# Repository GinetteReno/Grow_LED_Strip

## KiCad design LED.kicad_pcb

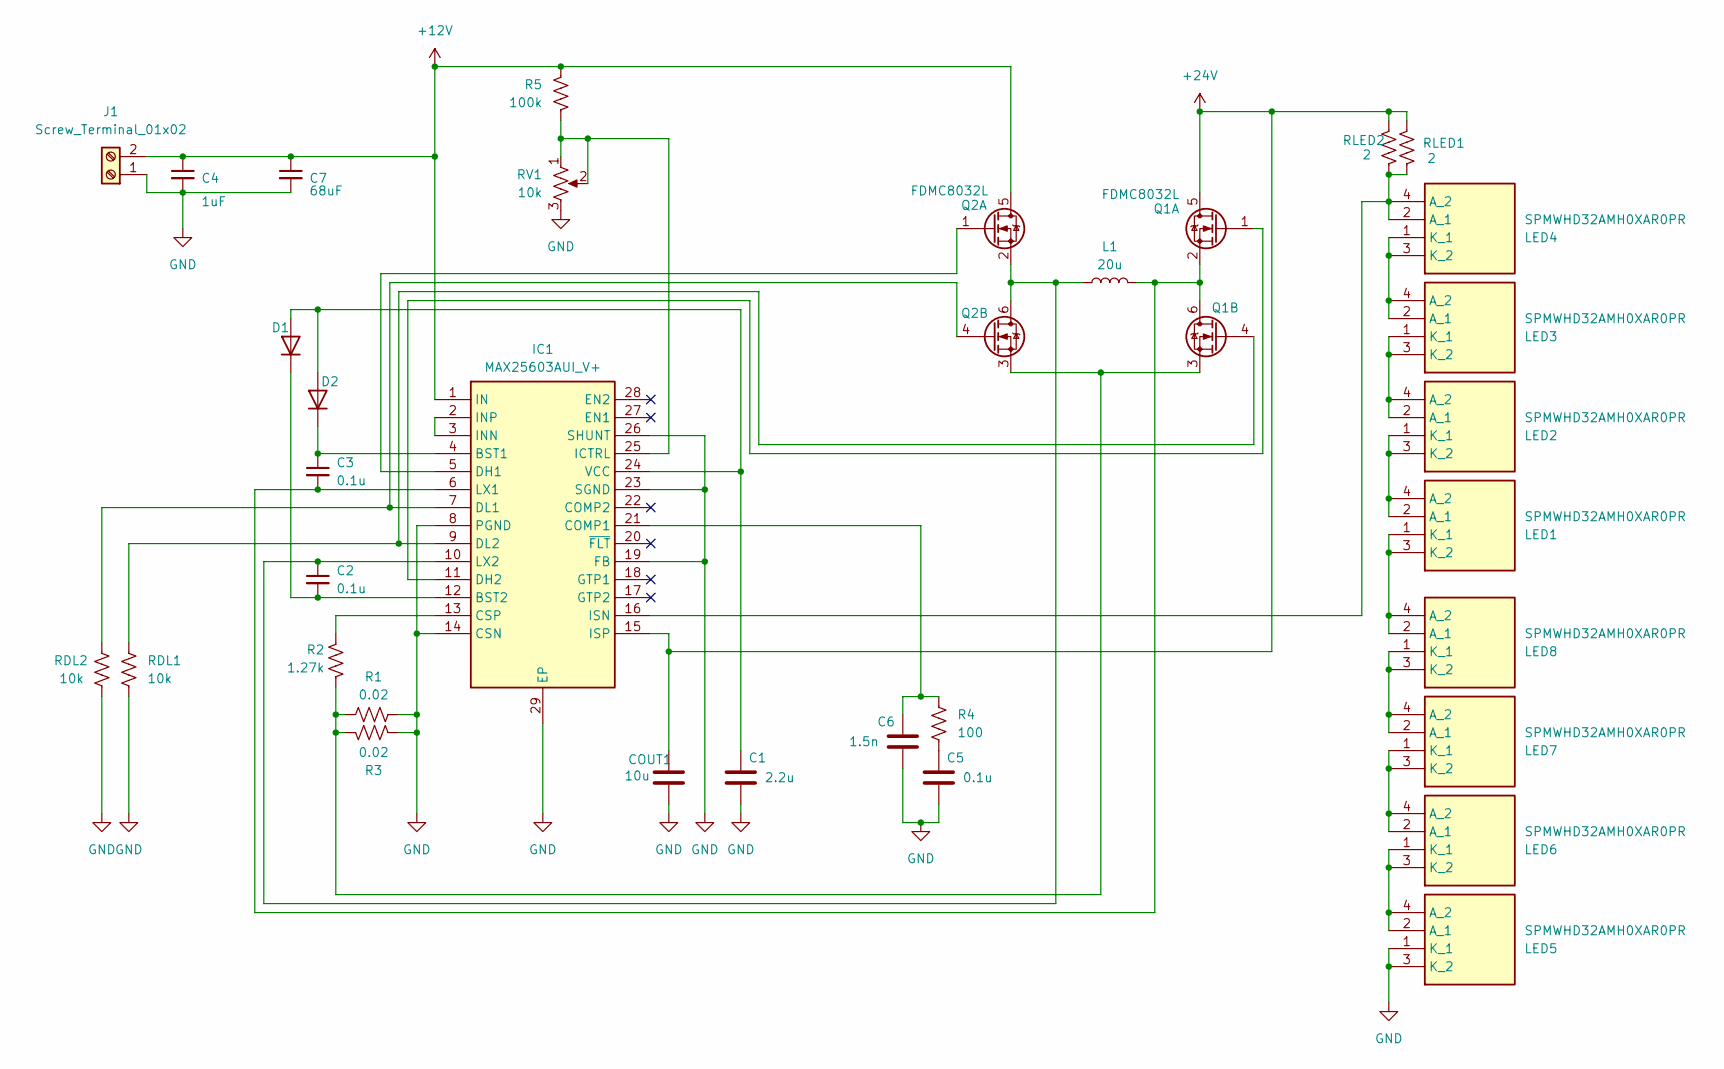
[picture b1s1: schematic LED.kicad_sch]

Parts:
C1: 2.2u; CAPC2012X140N
C2, C3, C5: 0.1u; CAPC2012X140N
C4: 1uF; CAPC2012X140N
C6: 1.5n; CAPC2012X140N
C7: 68uF; CP_Elec_6.3x5.4
COUT1: 10u; C_1206_3216Metric
D1, D2: D; D_SOD-123
IC1: MAX25603AUI_V+; SOP65P640X110-29N; Manufacturer_Part_Number MAX25603AUI/V+; Mouser Part Number 700-MAX25603AUI/V+
J1: Screw_Terminal_01x02; TerminalBlock_MetzConnect_Type086_RT03402HBLC_1x02_P3.81mm_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
L1: 20u; 7843332000
LED1, LED2, LED3, LED4, LED5, LED6, LED7, LED8: SPMWHD32AMH0XAR0PR; Manufacturer_Part_Number SPMWHD32AMH0XAR0PR
Q1, Q2: FDMC8032L; Fairchild_DualPower33-6_3x3mm
R1, R3: 0.02; R_1210_3225Metric
R2: 1.27k; R_0805_2012Metric
R4: 100; R_0805_2012Metric
R5: 100k; R_0805_2012Metric
RDL1, RDL2: 10k; R_0805_2012Metric
RLED1, RLED2: 2; R_0805_2012Metric
RV1: 10k; Potentiometer_Vishay_TS53YJ_Vertical

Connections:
+12V: C4.1, C7.1, IC1.1 (IN), J1.2, Q2.5 (D1), R5.1
+24V: COUT1.1, IC1.15 (ISP), Q1.5 (D1), RLED1.2, RLED2.2
GND: C1.2, C4.2, C5.2, C6.2, C7.2, COUT1.2, IC1.8 (PGND), IC1.14 (CSN), IC1.19 (FB), IC1.23 (SGND), IC1.26 (SHUNT), IC1.29 (EP), J1.1, LED5.1 (K_1), LED5.3 (K_2), R1.1, R3.1, RDL1.2, RDL2.2, RV1.3
unnamed: C5.1, R4.2
unnamed: C1.1, D1.2 (A), D2.2 (A), IC1.24 (VCC)
unnamed: C2.2, D1.1 (K), IC1.12 (BST2)
unnamed: C3.1, D2.1 (K), IC1.4 (BST1)
unnamed: C6.1, IC1.21 (COMP1), R4.1
unnamed: IC1.13 (CSP), R2.1
unnamed: IC1.5 (DH1), Q2.1 (G1)
unnamed: IC1.11 (DH2), Q1.1 (G1)
unnamed: IC1.7 (DL1), Q2.4 (G2), RDL2.1
unnamed: IC1.9 (DL2), Q1.4 (G2), RDL1.1
unnamed: IC1.25 (ICTRL), R5.2, RV1.1, RV1.2
unnamed: IC1.2 (INP), IC1.3 (INN)
unnamed: IC1.16 (ISN), LED4.2 (A_1), LED4.4 (A_2), RLED1.1, RLED2.1
unnamed: C3.2, IC1.6 (LX1), L1.2, Q1.2 (S1), Q1.6 (D2)
unnamed: C2.1, IC1.10 (LX2), L1.1, Q2.2 (S1), Q2.6 (D2)
unnamed: LED1.2 (A_1), LED1.4 (A_2), LED2.1 (K_1), LED2.3 (K_2)
unnamed: LED1.1 (K_1), LED1.3 (K_2), LED8.2 (A_1), LED8.4 (A_2)
unnamed: LED2.2 (A_1), LED2.4 (A_2), LED3.1 (K_1), LED3.3 (K_2)
unnamed: LED3.2 (A_1), LED3.4 (A_2), LED4.1 (K_1), LED4.3 (K_2)
unnamed: LED5.2 (A_1), LED5.4 (A_2), LED6.1 (K_1), LED6.3 (K_2)
unnamed: LED6.2 (A_1), LED6.4 (A_2), LED7.1 (K_1), LED7.3 (K_2)
unnamed: LED7.2 (A_1), LED7.4 (A_2), LED8.1 (K_1), LED8.3 (K_2)
unnamed: Q1.3 (S2), Q2.3 (S2), R1.2, R2.2, R3.2

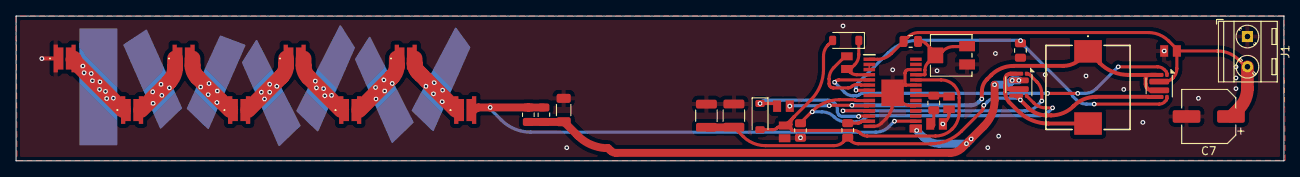
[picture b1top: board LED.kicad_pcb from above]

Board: 2 copper layers, 159.8 x 18.2 mm, 33 parts (0 on the bottom side), 26 nets.

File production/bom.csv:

Designator,Footprint,Quantity,Value,LCSC Part #
C1,CAPC2012X140N,1,2.2u,
"C2, C3, C5",CAPC2012X140N,3,0.1u,
C4,CAPC2012X140N,1,1uF,
C6,CAPC2012X140N,1,1.5n,
C7,CP_Elec_6.3x5.4,1,68uF,
COUT1,1206,1,10u,
"D1, D2",D_SOD-123,2,D,
IC1,SOP65P640X110-29N,1,MAX25603AUI_V+,
J1,TerminalBlock_MetzConnect_Type086_RT03402HBLC_1x02_P3.81mm_Horizontal,1,Screw_Terminal_01x02,
L1,7843332000,1,20u,
"LED1, LED2, LED3, LED4, LED5, LED6, LED7, LED8",SPMWHD32AMH0XAR0PR,8,SPMWHD32AMH0XAR0PR,
"Q1, Q2",Fairchild_DualPower33-6_3x3mm,2,FDMC8032L,
"R1, R3",1210,2,0.02,
R2,0805,1,1.27k,
R4,0805,1,100,
R5,0805,1,100k,
"RDL1, RDL2",0805,2,10k,
"RLED1, RLED2",0805,2,2,
RV1,Potentiometer_Vishay_TS53YJ_Vertical,1,10k,

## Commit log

2024-11-12 working for free
2024-11-13 placed leds
2024-11-13 more free work (done pcb)
